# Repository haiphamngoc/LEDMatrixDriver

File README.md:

# LEDMatrixDriver
A LED matrix driver for Arduino

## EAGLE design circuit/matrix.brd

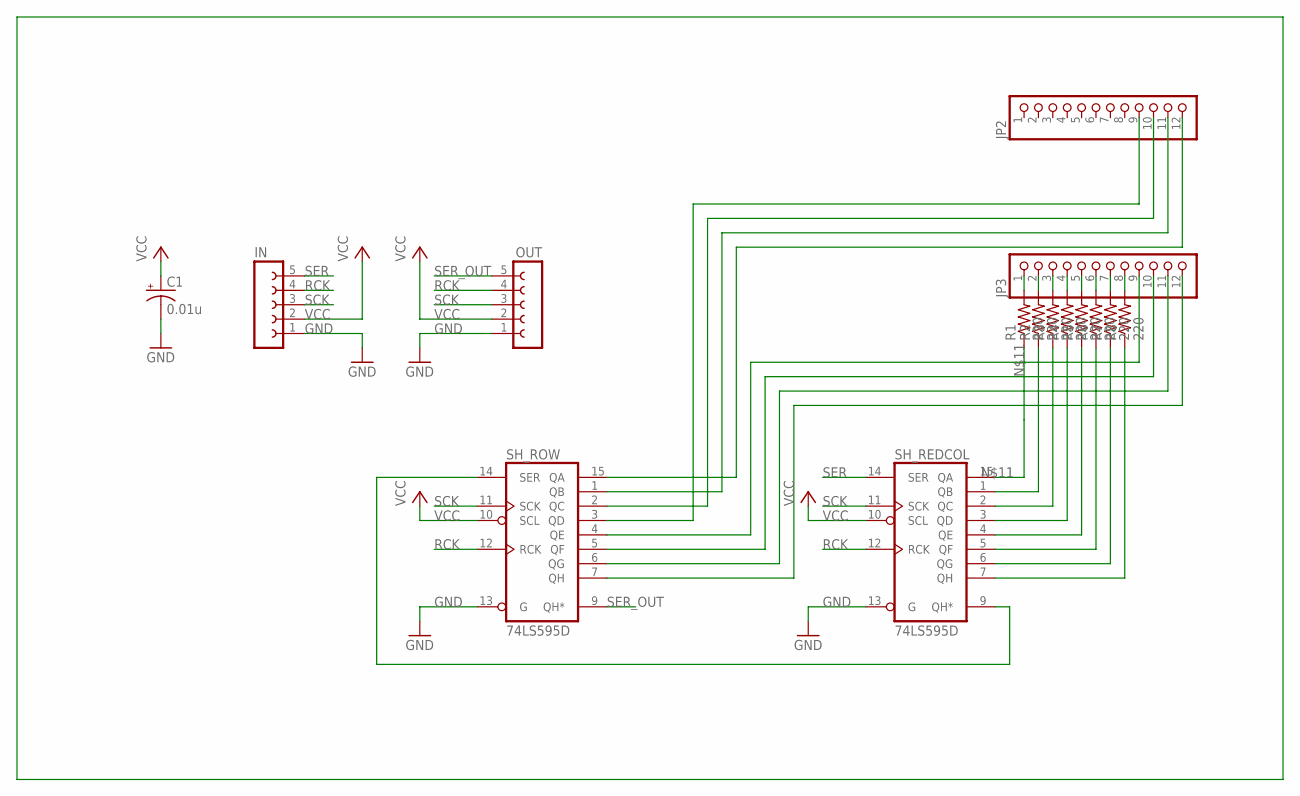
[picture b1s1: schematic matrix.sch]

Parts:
C1: 0.01u; E2,5-5
IN: FE05W
JP2, JP3: PINHD-1X12-CB; 1X12-CB
OUT: FE05W
R1, R2, R3, R4, R5, R6, R7, R8: 220; R0603
SH_REDCOL: 74LS595D; SO16
SH_ROW: 74LS595D; SO16

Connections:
GND: C1.-, IN.1, OUT.1, SH_REDCOL.8 (GND), SH_REDCOL.13 (G), SH_ROW.8 (GND), SH_ROW.13 (G)
unnamed: JP3.1, R1.2
unnamed: R4.1, SH_REDCOL.3 (QD)
unnamed: R5.1, SH_REDCOL.4 (QE)
unnamed: JP2.12, SH_ROW.15 (QA)
unnamed: JP2.11, SH_ROW.1 (QB)
unnamed: JP2.10, SH_ROW.2 (QC)
unnamed: JP2.9, SH_ROW.3 (QD)
unnamed: JP3.9, SH_ROW.4 (QE)
unnamed: R1.1, SH_REDCOL.15 (QA)
unnamed: R2.1, SH_REDCOL.1 (QB)
unnamed: R3.1, SH_REDCOL.2 (QC)
unnamed: R6.1, SH_REDCOL.5 (QF)
unnamed: R7.1, SH_REDCOL.6 (QG)
unnamed: R8.1, SH_REDCOL.7 (QH)
unnamed: JP3.10, SH_ROW.5 (QF)
unnamed: JP3.11, SH_ROW.6 (QG)
unnamed: JP3.12, SH_ROW.7 (QH)
unnamed: JP3.2, R2.2
unnamed: JP3.3, R3.2
unnamed: JP3.4, R4.2
unnamed: JP3.5, R5.2
unnamed: JP3.6, R6.2
unnamed: JP3.7, R7.2
unnamed: JP3.8, R8.2
RCK: IN.4, OUT.4, SH_REDCOL.12 (RCK), SH_ROW.12 (RCK)
SCK: IN.3, OUT.3, SH_REDCOL.11 (SCK), SH_ROW.11 (SCK)
SER: IN.5, SH_REDCOL.14 (SER)
SER2: SH_REDCOL.9 (QH*), SH_ROW.14 (SER)
SER_OUT: OUT.5, SH_ROW.9 (QH*)
VCC: C1.+, IN.2, OUT.2, SH_REDCOL.10 (SCL), SH_REDCOL.16 (VCC), SH_ROW.10 (SCL), SH_ROW.16 (VCC)

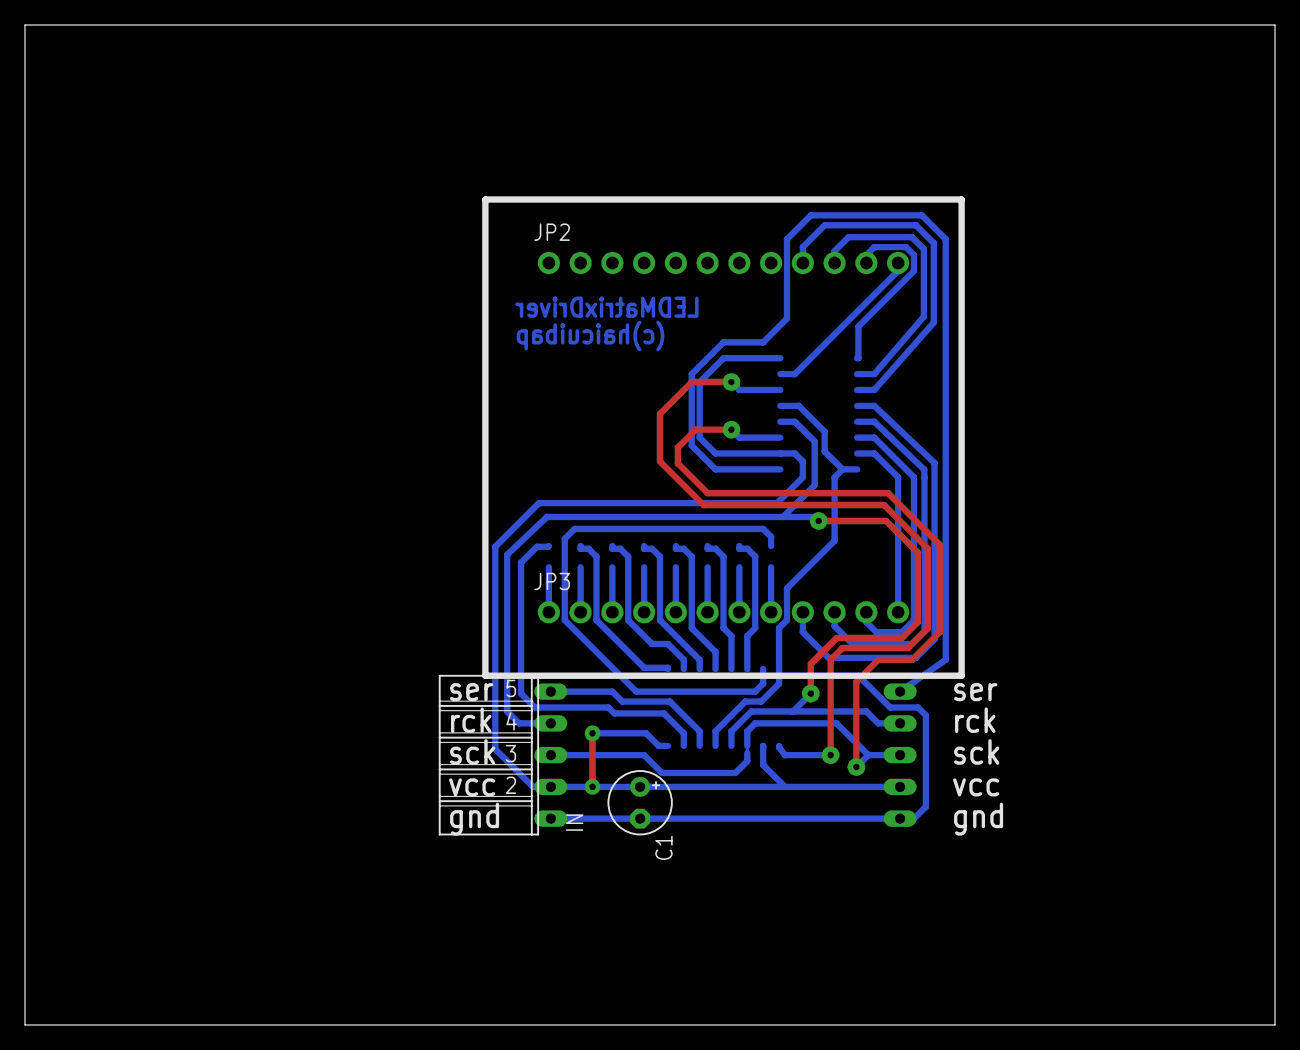
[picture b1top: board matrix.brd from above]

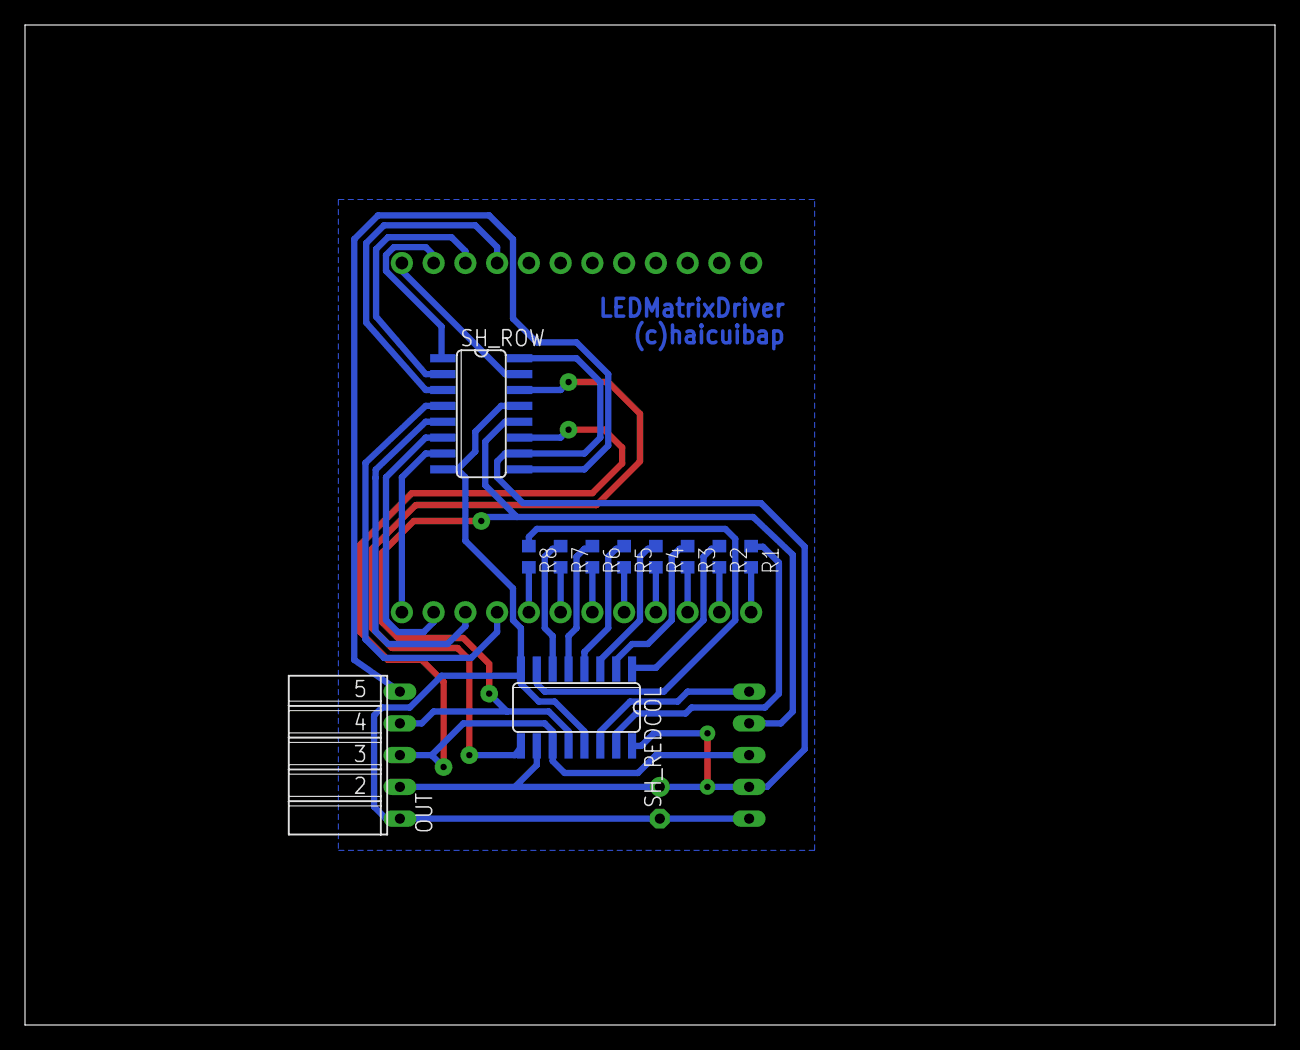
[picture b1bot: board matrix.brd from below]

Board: 2 copper layers, 100.0 x 80.0 mm, 15 parts (11 on the bottom side), 31 nets.

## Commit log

2014-12-29 :space_invader: Added .gitattributes
2015-03-30 Add LICENSE file via addalicense.com
2015-03-30 Initial releases
2015-03-30 Rename LEDMatrix.cpp to libraries/LEDMatrix.cpp
2015-03-30 Rename LEDMatrix.h to libraries/LEDMatrix.h
2015-03-30 Rename examples/drawBitmap/drawBitmap.ino to libraries/examples/drawBitmap/drawBitmap.ino
2015-06-23 Adding EAGLE files
